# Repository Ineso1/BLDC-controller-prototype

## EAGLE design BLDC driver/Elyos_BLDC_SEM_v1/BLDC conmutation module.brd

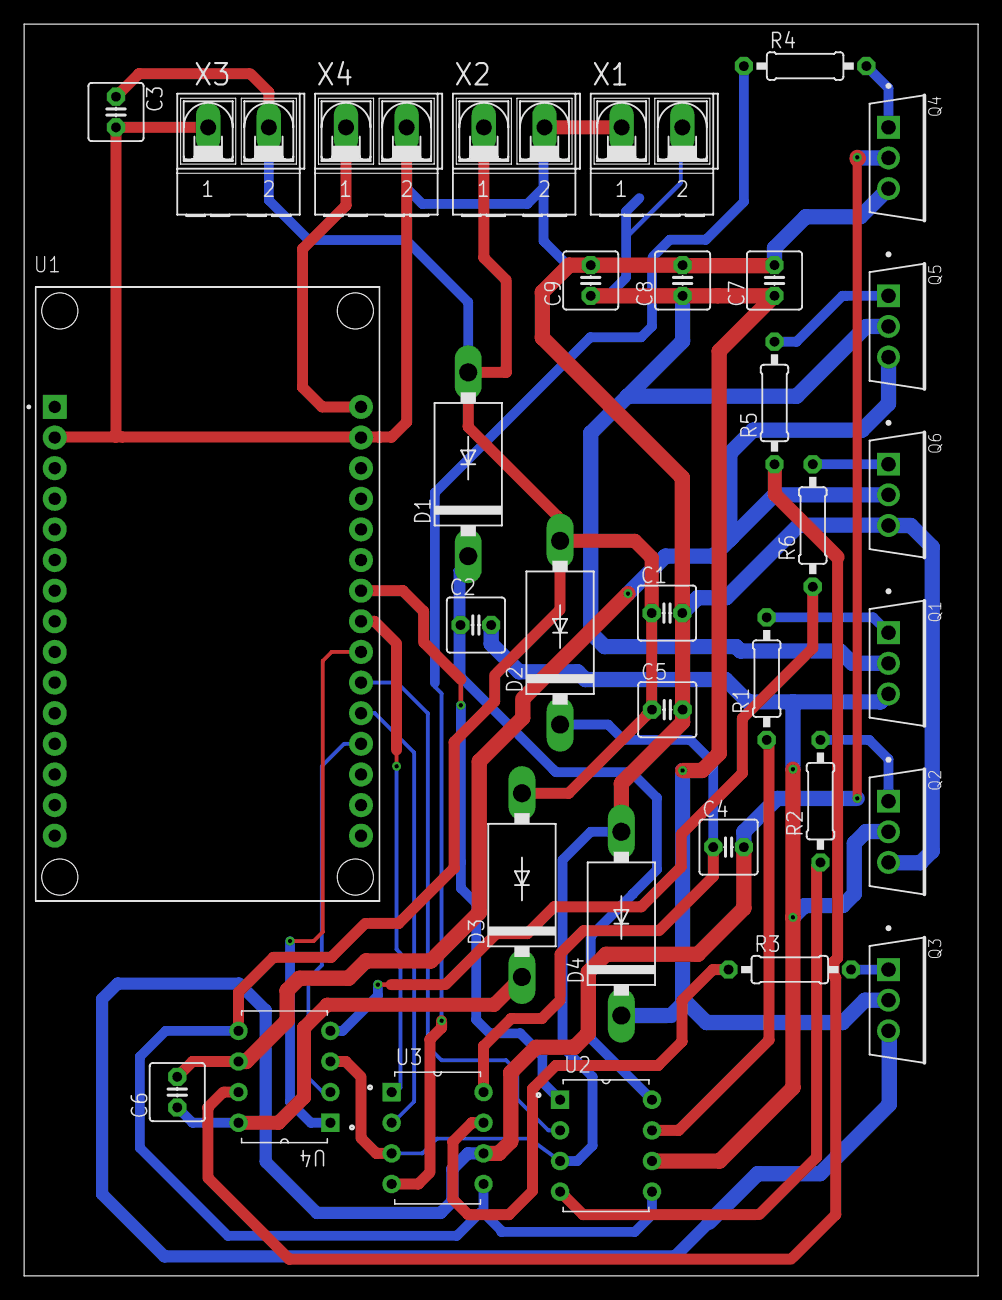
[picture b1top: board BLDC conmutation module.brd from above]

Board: 2 copper layers, 79.1 x 103.8 mm, 33 parts (0 on the bottom side), 28 nets.

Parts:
C1, C2, C3, C4, C5, C6: 1nF; C025-050X050
C7, C8, C9: 480uF; C025-050X050
D1, D2, D3, D4: 1N5400; DO201-15
Q1, Q2, Q3, Q4, Q5, Q6: INFINEON_IRFB3077PBFINFINEON_IRFB3077PBF_0_0; INFINEON_IRFB3077PBF_0
R1, R2, R3, R4, R5, R6: 100; 0207/10
U1: ESP32-DEVKIT-V1; MODULE_ESP32_DEVKIT_V1
U2, U3, U4: IR2183; DIP762W45P254L1092H533Q8
X1, X2, X3, X4: AK500/2-H

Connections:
GND: C1.2, C3.2, C5.2, C7.2, C8.2, C9.2, D4.A, Q2.3, Q4.3, Q6.3, U1.2, U1.29, U2.3, U3.3, U4.3, X1.1, X2.2, X3.1, X4.2
HIN_1: U1.24, U2.1
HIN_2: U1.23, U3.1
HIN_3: U1.22, U4.1
HO_1: R1.1, U2.7
HO_2: R3.1, U3.7
HO_3: R5.1, U4.7
LIN_1: U1.21, U2.2
LIN_2: U1.20, U3.2
LIN_3: U1.19, U4.2
LO_1: R2.1, U2.4
LO_2: R4.1, U3.4
LO_3: R6.1, U4.4
unnamed: C4.1, D2.C, U3.8
unnamed: C6.1, D3.C, U4.8
unnamed: C2.1, D1.C, U2.8
unnamed: Q3.1, R3.2
unnamed: Q1.1, R1.2
unnamed: Q2.1, R2.2
unnamed: Q4.1, R4.2
unnamed: Q5.1, R5.2
unnamed: Q6.1, R6.2
PHASE_1: C2.2, Q1.3, Q2.2, U2.6
PHASE_2: C4.2, Q3.3, Q4.2, U3.6
PHASE_3: C6.2, Q5.3, Q6.2, U4.6
RAW_VCC: C7.1, C8.1, C9.1, D4.C, Q1.2, Q3.2, Q5.2, X1.2
VCC_5V: U1.30, X4.1
VCC_15V: C1.1, C3.1, C5.1, D1.A, D2.A, D3.A, U2.5, U3.5, U4.5, X2.1, X3.2

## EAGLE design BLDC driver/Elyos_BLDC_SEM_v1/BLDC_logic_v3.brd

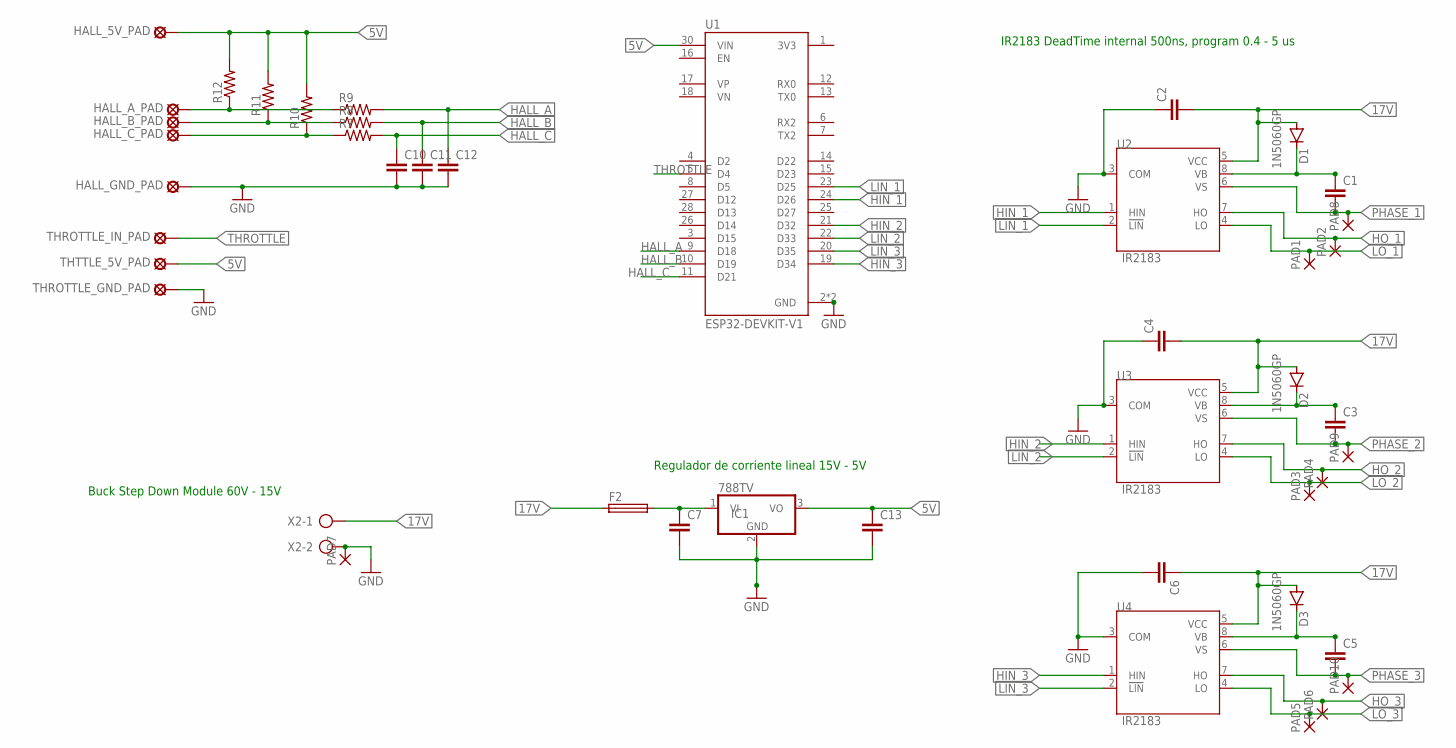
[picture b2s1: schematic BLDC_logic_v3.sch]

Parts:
C1, C2, C3, C4, C5, C6, C7, C10, C11, C12, C13: C-EU025-030X050; C025-030X050
D1, D2, D3: 1N5060GP; DO15-12
F2: SH22,5
HALL_5V_PAD: MCS08
HALL_A_PAD: MCS08
HALL_B_PAD: MCS08
HALL_C_PAD: MCS08
HALL_GND_PAD: MCS08
IC1: 788TV; TO220V
PAD1, PAD2, PAD3, PAD4, PAD5, PAD6, PAD7, PAD8, PAD9, PAD10: 3,81/1,4
R7, R8, R9, R10, R11, R12: R-US_0204/7; 0204/7
THROTTLE_GND_PAD: MCS08
THROTTLE_IN_PAD: MCS08
THTTLE_5V_PAD: MCS08
U1: ESP32-DEVKIT-V1; MODULE_ESP32_DEVKIT_V1
U2, U3, U4: IR2183; DIP762W45P254L1092H533Q8
X2: AK500/2-H

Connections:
5V: C13.1, HALL_5V_PAD.MP, IC1.3 (VO), R10.2, R11.2, R12.2, THTTLE_5V_PAD.MP, U1.30 (VIN)
17V: C2.2, C4.2, C6.1, D1.A, D2.A, D3.A, F2.1, U2.5 (VCC), U3.5 (VCC), U4.5 (VCC), X2.1
GND: C2.1, C4.1, C6.2, C7.2, C10.2, C11.2, C12.2, C13.2, HALL_GND_PAD.MP, IC1.2 (GND), PAD7.1, THROTTLE_GND_PAD.MP, U1.2 (GND), U1.29 (GND), U2.3 (COM), U3.3 (COM), U4.3 (COM), X2.2
HALL_A: C12.1, R9.2, U1.9 (D18)
HALL_B: C11.1, R8.2, U1.10 (D19)
HALL_C: C10.1, R7.2, U1.11 (D21)
HIN_1: U1.24 (D26), U2.1 (HIN)
HIN_2: U1.21 (D32), U3.1 (HIN)
HIN_3: U1.19 (D34), U4.1 (HIN)
HO_1: PAD2.1, U2.7 (HO)
HO_2: PAD4.1, U3.7 (HO)
HO_3: PAD6.1, U4.7 (HO)
LIN_1: U1.23 (D25), U2.2 (!LIN)
LIN_2: U1.22 (D33), U3.2 (!LIN)
LIN_3: U1.20 (D35), U4.2 (!LIN)
LO_1: PAD1.1, U2.4 (LO)
LO_2: PAD3.1, U3.4 (LO)
LO_3: PAD5.1, U4.4 (LO)
unnamed: C3.1, D2.C, U3.8 (VB)
unnamed: C5.1, D3.C, U4.8 (VB)
unnamed: C1.1, D1.C, U2.8 (VB)
unnamed: C7.1, F2.2, IC1.1 (VI)
unnamed: HALL_A_PAD.MP, R9.1, R12.1
unnamed: HALL_B_PAD.MP, R8.1, R11.1
unnamed: HALL_C_PAD.MP, R7.1, R10.1
PHASE_1: C1.2, PAD8.1, U2.6 (VS)
PHASE_2: C3.2, PAD9.1, U3.6 (VS)
PHASE_3: C5.2, PAD10.1, U4.6 (VS)
THROTTLE: THROTTLE_IN_PAD.MP, U1.5 (D4)

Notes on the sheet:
IR2183 DeadTime internal 500ns, program 0.4 - 5 us
Buck Step Down Module 60V - 15V
Regulador de corriente lineal 15V - 5V

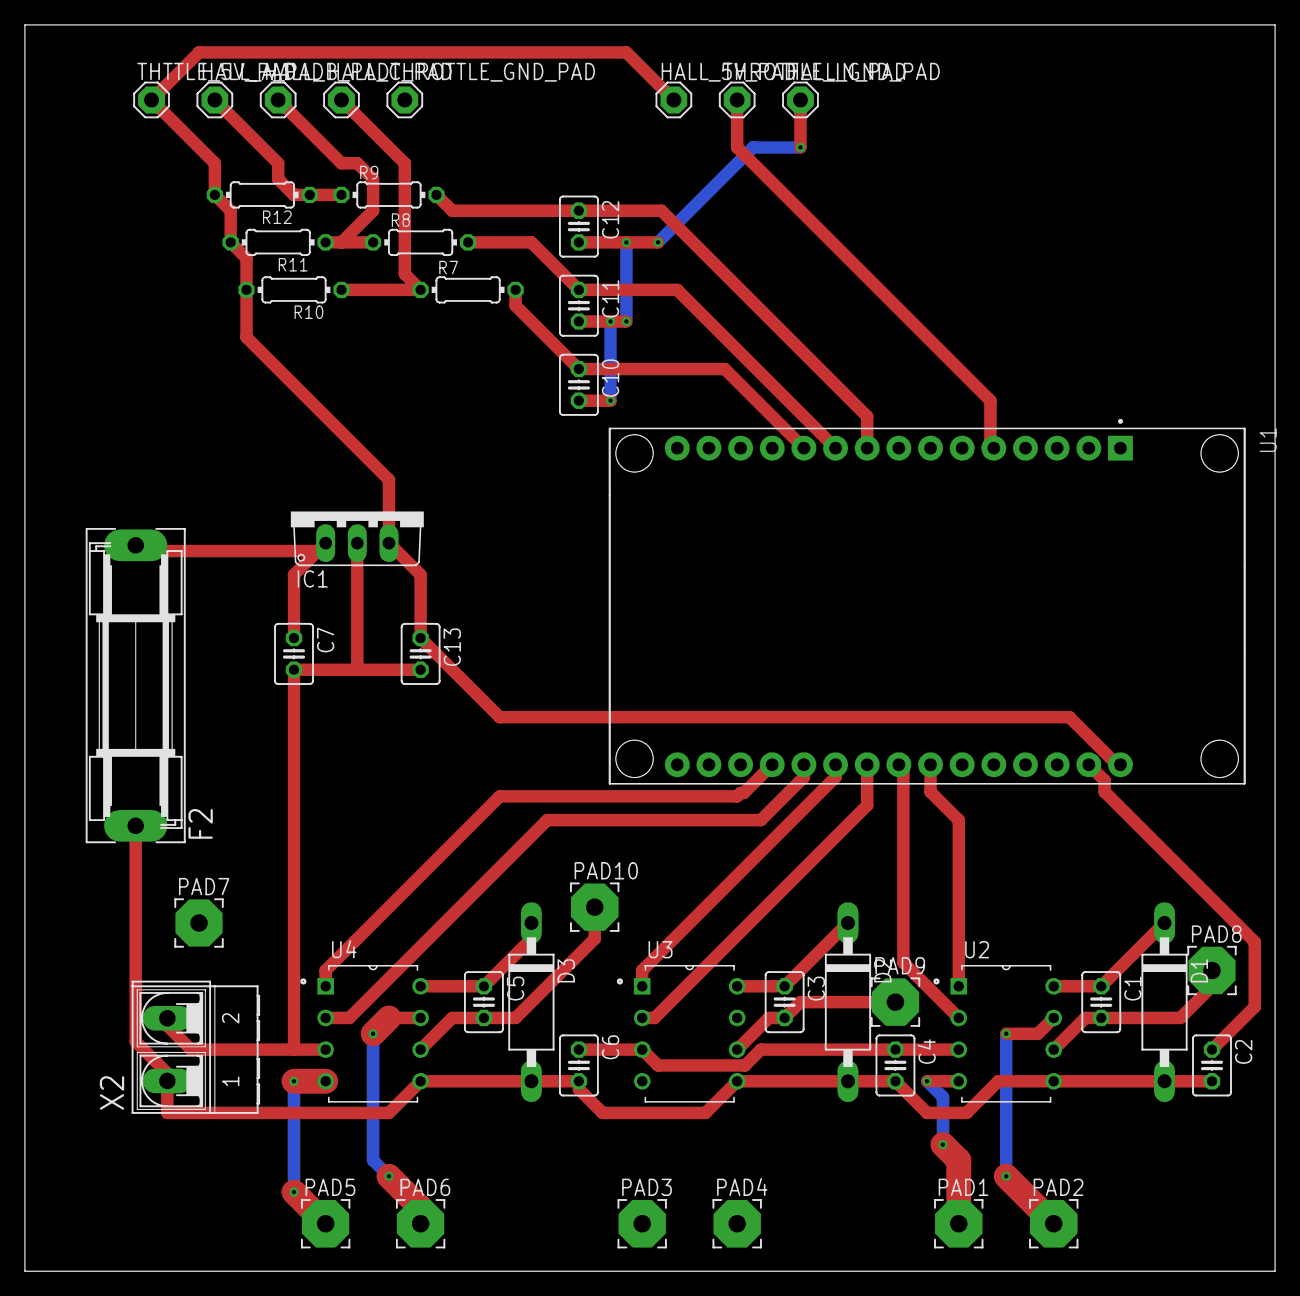
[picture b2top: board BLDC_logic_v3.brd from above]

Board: 2 copper layers, 100.3 x 100.0 mm, 45 parts (0 on the bottom side), 29 nets.

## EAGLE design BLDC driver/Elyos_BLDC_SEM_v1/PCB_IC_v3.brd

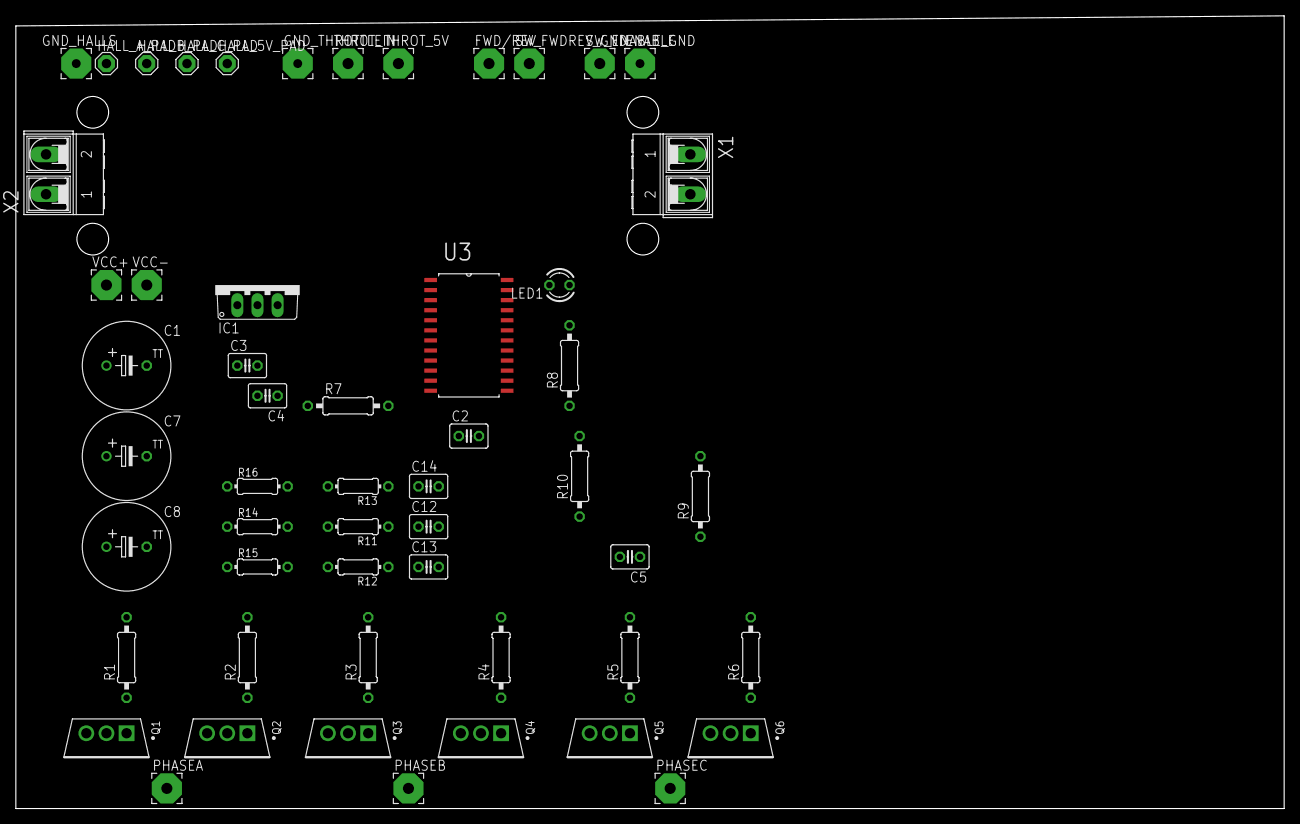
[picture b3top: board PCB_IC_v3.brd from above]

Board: 2 copper layers, 160.0 x 100.0 mm, 54 parts (0 on the bottom side), 35 nets, no tracks yet.

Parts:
C1, C7, C8: TT5D11
C2, C3, C4, C5, C12, C13, C14: C025-030X050
ENABLE: 3,81/1,1
FWD/REV: 3,81/1,4
GND_HALLS: 3,81/1,1
GND_THROTTLE: 3,81/1,1
HALL_5V_PAD: MCS08
HALL_A_PAD: MCS08
HALL_B_PAD: MCS08
HALL_C_PAD: MCS08
IC1: 7805TV; TO220V
LED1: TLLY4400; LED3MM
PHASEA: 3,81/1,4
PHASEB: 3,81/1,4
PHASEC: 3,81/1,4
Q1, Q2, Q3, Q4, Q5, Q6: INFINEON_IRFB7730PBFINFINEON_IRFB7730PBF_0_0; INFINEON_IRFB7730PBF_0
R1, R2, R3, R4, R5, R6, R7: 4.7k; 0207/10
R8, R9, R10: 0207/10
R11, R12, R13, R14, R15, R16: 0204/7
SW_ENABLE_GND: 3,81/1,4
SW_FWDREV_GND: 3,81/1,4
THROT_5V: 3,81/1,4
THROT_IN: 3,81/1,4
U3: MC33035DWG; SOIC127P1030X265-24N
VCC+: 3,81/1,4
VCC-: 3,81/1,4
X1, X2: AK500/2-H

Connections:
5V: C4.1, HALL_5V_PAD.MP, IC1.3, R7.1, R14.2, R15.2, R16.2, THROT_5V.1, U3.8
15V: U3.17, U3.18, X2.1
GND: C2.2, C12.2, C13.2, C14.2, LED1.K, SW_ENABLE_GND.1, SW_FWDREV_GND.1, U3.15, U3.16, U3.22, U3.23, X1.1, X2.2
I_SENSE_NOFILTER: C1.-, C7.-, C8.-, Q2.3, Q4.3, Q6.3, VCC-.1
unnamed: C1.+, C7.+, C8.+, Q1.2, Q3.2, Q5.2, VCC+.1
unnamed: Q1.1, R1.1
unnamed: FWD/REV.1, U3.3
unnamed: ENABLE.1, U3.7
unnamed: Q2.1, R2.1
unnamed: Q3.1, R3.1
unnamed: Q4.1, R4.1
unnamed: Q5.1, R5.1
unnamed: Q6.1, R6.1
unnamed: U3.12, U3.13
unnamed: C3.2, C4.2, GND_HALLS.1, GND_THROTTLE.1, IC1.2
unnamed: R9.2, R10.2
unnamed: C3.1, IC1.1
unnamed: R8.1, U3.14
unnamed: THROT_IN.1, U3.11
unnamed: C2.1, R7.2, U3.10
unnamed: LED1.A, R8.2
unnamed: C5.1, R9.1
unnamed: HALL_A_PAD.MP, R13.1, R16.1
unnamed: C5.2, R10.1
unnamed: HALL_B_PAD.MP, R12.1, R15.1
unnamed: HALL_C_PAD.MP, R11.1, R14.1
OUT_A_HIGH: R1.2, U3.2
OUT_A_LOW: R2.2, U3.21
OUT_B_LOW: R4.2, U3.20
OUT_C_LOW: R6.2, U3.19
PAD_HALL_A: C14.1, R13.2, U3.4
PAD_HALL_B: C13.1, R12.2, U3.5
PAD_HALL_C: C12.1, R11.2, U3.6
PHASE_B: PHASEB.1, Q3.3, Q4.2
PHASE_C: PHASEC.1, Q5.3, Q6.2
